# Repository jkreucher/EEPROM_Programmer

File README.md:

# Simple EEPROM Programmer

Copyright 2021 Jannik Kreucher

## Table of Contents
 - [Project](#project)
 - [Dependencies](#dependencies)
 - [Make](#make)
 - [Flash EEPROM](#flash-eeprom)
 - [Schematic](#schematic)
   - [Processor](#micro-processor)
   - [Shift Registers](#shift-registers)
   - [EEPROM](#eeprom)
 - [PCB](#pcb)
 - [Enclosure](#enclosure)
 - [License](#license)

## Project

I created this programmer for my personal Z80 project. Since commerical programmers are fairly expensive I created my own simple programmer. It is nothing fancy and just supports a single family of [EEPROMs](https://en.wikipedia.org/wiki/EEPROM). It does not have support for a higher programming voltage and is limited for +5V EEPROMs.

This simple programmer supports following EEPROMs:
 - [28c64 (8k)](http://ww1.microchip.com/downloads/en/devicedoc/doc0001h.pdf)
 - [28c256 (32k)](http://ww1.microchip.com/downloads/en/DeviceDoc/doc0006.pdf)

## Dependencies

To compile the code you need to have following tools installed:
 - avr-gcc (with avr-libs)
 - avrdude
 - uisp

The programmer flash tool uses [Python3](https://www.python.org/) and [pySerial](https://pyserial.readthedocs.io/en/latest/pyserial.html):
 - python3
 - python3-serial

The Makefile contains a command to install everything needed:
```
cd code
sudo make tools
```

## Make

First compile the ATmega code. Execute following in the project root folder:
```
cd code
make
```

Now flash the compiled code to the programmer. *Connect the ISP-Programmer* and execute:
```
make fuses
make upload
```
I am using a USBasp Programmer. **Note: Notch on ISP-Programmer must be facing the ATmega8 chip (U1) while flashing firmware.**

## Flash EEPROM

**Note: Firmware needs to be flashed beforehand !**

To flash your binary file to the EEPROM inserted type:
```
cd code
chmod +x eeprom.py
./eeprom.py -e -o -p /dev/ttyACM0 -b 115200 -w <binaryfile.bin>
```

For more information:
```
./eeprom.py -h
```

## Schematic

### Micro Processor
The micro processor used in this project is the popular [ATmega8 (U1)](https://ww1.microchip.com/downloads/en/DeviceDoc/Atmel-2486-8-bit-AVR-microcontroller-ATmega8_L_datasheet.pdf), a cheaper version of the ATmega328 used in the [Arduino Uno](https://store.arduino.cc/arduino-uno-rev3). It handles everything: the serial communication, address bus and the data bus. U2 (MCP2221) handles the USB to UART conversion so no external ftdi cable is needed. The supply voltage is conveniantly given by the USB port also. Because data bus of the EEPROM is bidirectional it is directly connected to the processor. The micro processor needs to handle setting the bus as input or output. See [`eeprom.c`](code/eeprom.c) for everything I/O related. The UART is handled in [`uart.c`](code/uart.c). And the communication protocol is defined in [`parser.c`](code/parser.c) and in [`main.c`](code/main.c).

### Shift Registers
The shift registers (U3, U4) are utilized to expand the IO of the processor. Just 3 bits are needed to set the address bus to the target address. Since the address bus is only one way no data needs to be read from the address bus thus making shift registers the obvious choice for this situation. See [`eeprom.c: addrbus_set()`](code/eeprom.c) for how the data is latched.

### EEPROM

The EEPROM uses a parallel interface for communication. The address bus (A0-A14) is a parallel input which sets the memory location to read or write. The control lines ~WE and ~OE (active low) tell the EEPROM to read or write from/to the memory. The data is read from or sent out the parallel data bus (D0-D7) depending on the state of the control lines. Some EEPROMs have Write-Protect enabled. A algorithm (see datasheet) is implemented to deactivate write protection. See [`eeprom.c: eeprom_disable_protect()`](code/eeprom.c) for how this works.

## PCB

Note: The pcb is designed so that the top layer represents jumpers. The vias are large enough to stick a wire through.

For the schematic and pcb layout I used [KiCad](https://kicad.org/), a very awsome open source EDA. The clearances and spaces are designed for diy home etching so nothing really fancy. See [`eeprom_programmer_bom.pdf`](bom/eeprom_programmer_bom.pdf) for the bill of materials. At the moment the whole project would cost you around 26€ plus a weekend of time.

## Enclosure

The very simple, easy and fast to print enclosure consists of two parts which sandwhich the pcb. Needed are just *4x M3,5x12mm* wood screws to assemble the enclosure.

## License

[MIT](LICENSE) Jannik Kreucher

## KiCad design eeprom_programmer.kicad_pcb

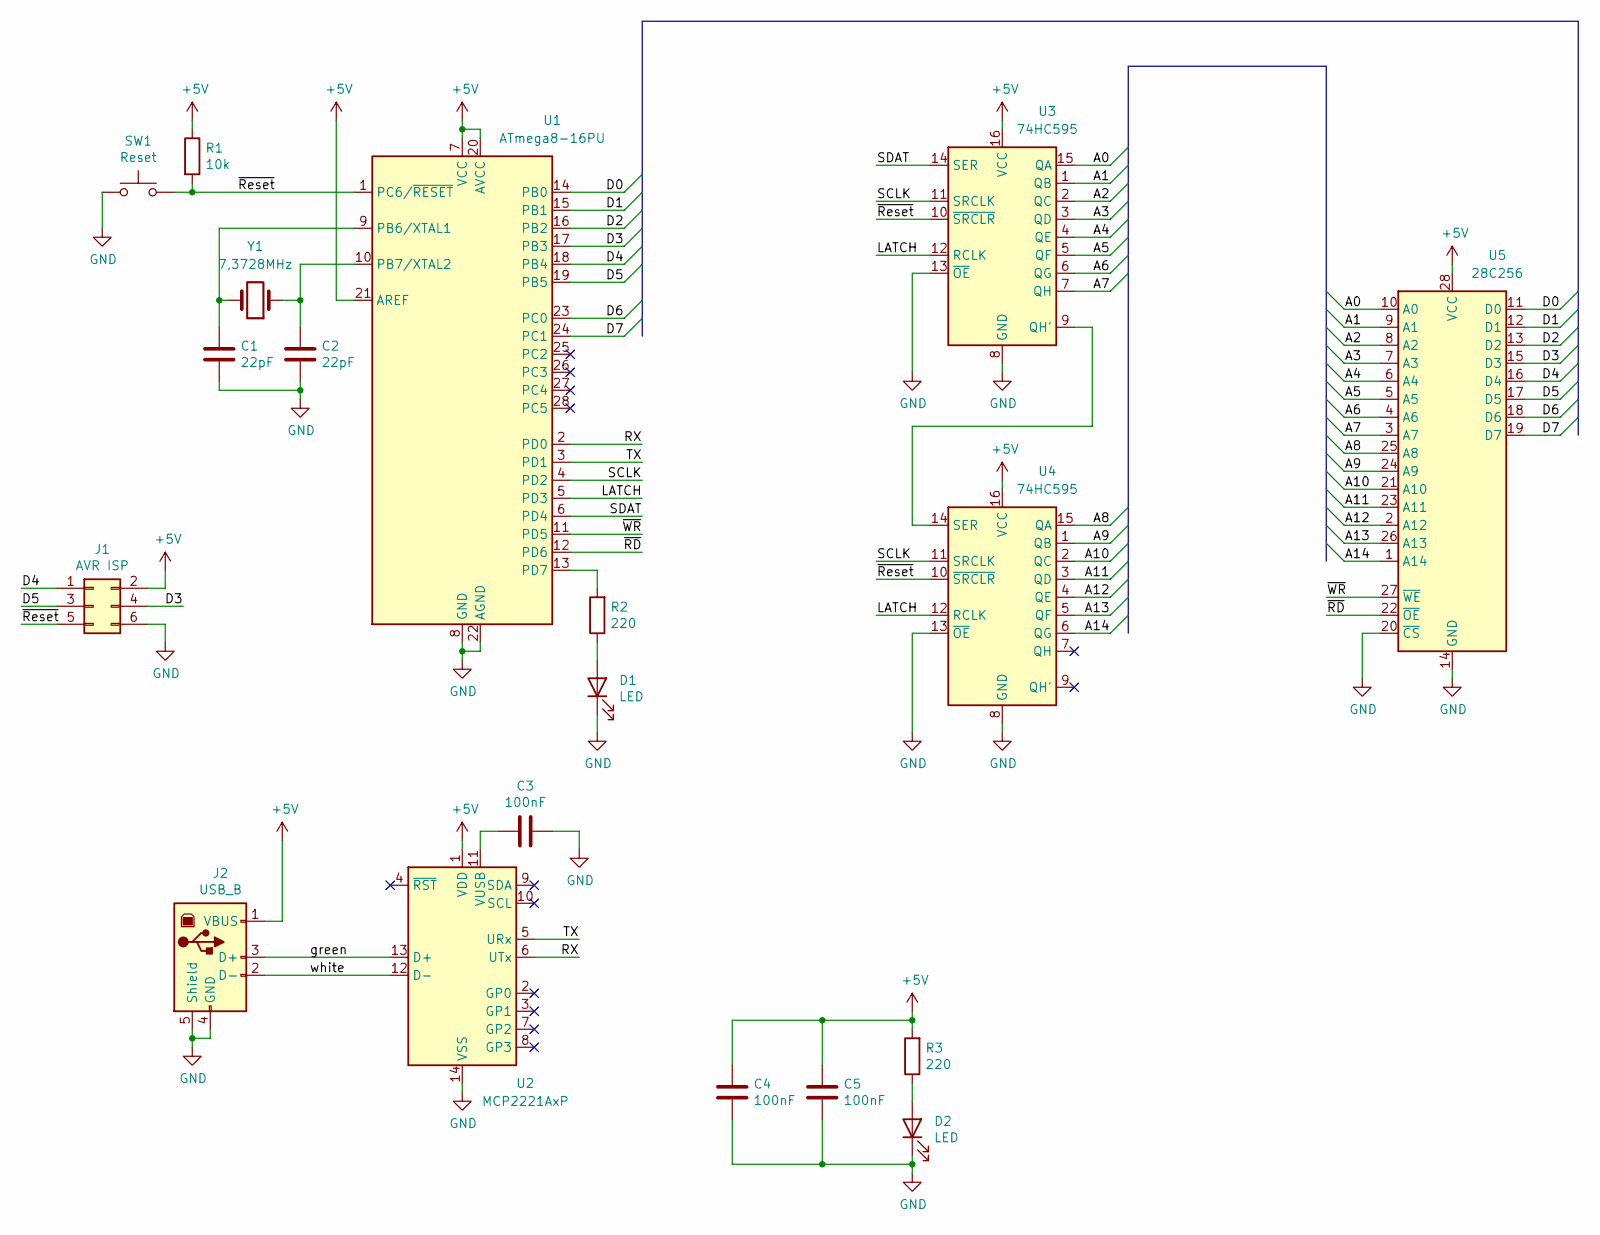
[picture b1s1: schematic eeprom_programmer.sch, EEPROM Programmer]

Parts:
C1, C2: 22pF; C_Disc_D3.0mm_W2.0mm_P2.50mm
C3, C4, C5: 100nF; C_Disc_D3.0mm_W2.0mm_P2.50mm
D1, D2: LED; LED_D5.0mm
J1: AVR ISP; PinHeader_2x03_P2.54mm_Vertical
J2: USB_B; USB_B_Lumberg_2411_02_Horizontal
R1: 10k; R_Axial_DIN0207_L6.3mm_D2.5mm_P10.16mm_Horizontal
R2, R3: 220; R_Axial_DIN0207_L6.3mm_D2.5mm_P10.16mm_Horizontal
SW1: Reset; SW_PUSH_6mm
U1: ATmega8-16PU; DIP-28_W7.62mm_LongPads
U2: MCP2221AxP; DIP-14_W7.62mm_LongPads
U3, U4: 74HC595; DIP-16_W7.62mm_LongPads
U5: 28C256; DIP-28_W15.24mm_ZIF_LongPads
Y1: 7,3728MHz; Crystal_HC49-U_Vertical

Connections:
+5V: C4.1, C5.1, J1.2, J2.1 (VBUS), R1.1, R3.2, U1.7 (VCC), U1.20 (AVCC), U1.21 (AREF), U2.1 (VDD), U3.16 (VCC), U4.16 (VCC), U5.28 (VCC)
/A0: U3.15 (QA), U5.10 (A0)
/A1: U3.1 (QB), U5.9 (A1)
/A2: U3.2 (QC), U5.8 (A2)
/A3: U3.3 (QD), U5.7 (A3)
/A4: U3.4 (QE), U5.6 (A4)
/A5: U3.5 (QF), U5.5 (A5)
/A6: U3.6 (QG), U5.4 (A6)
/A7: U3.7 (QH), U5.3 (A7)
/A8: U4.15 (QA), U5.25 (A8)
/A9: U4.1 (QB), U5.24 (A9)
/A10: U4.2 (QC), U5.21 (A10)
/A11: U4.3 (QD), U5.23 (A11)
/A12: U4.4 (QE), U5.2 (A12)
/A13: U4.5 (QF), U5.26 (A13)
/A14: U4.6 (QG), U5.1 (A14)
/D0: U1.14 (PB0), U5.11 (D0)
/D1: U1.15 (PB1), U5.12 (D1)
/D2: U1.16 (PB2), U5.13 (D2)
/D3: J1.4, U1.17 (PB3), U5.15 (D3)
/D4: J1.1, U1.18 (PB4), U5.16 (D4)
/D5: J1.3, U1.19 (PB5), U5.17 (D5)
/D6: U1.23 (PC0), U5.18 (D6)
/D7: U1.24 (PC1), U5.19 (D7)
/LATCH: U1.5 (PD3), U3.12 (RCLK), U4.12 (RCLK)
/RX: U1.2 (PD0), U2.6 (UTx)
/SCLK: U1.4 (PD2), U3.11 (SRCLK), U4.11 (SRCLK)
/SDAT: U1.6 (PD4), U3.14 (SER)
/TX: U1.3 (PD1), U2.5 (URx)
/green: J2.3 (D+), U2.13 (D+)
/white: J2.2 (D-), U2.12 (D-)
/~RD: U1.12 (PD6), U5.22 (~OE)
/~Reset: J1.5, R1.2, SW1.2, U1.1 (PC6/~RESET), U3.10 (~SRCLR), U4.10 (~SRCLR)
/~WR: U1.11 (PD5), U5.27 (~WE)
GND: C1.2, C2.2, C3.1, C4.2, C5.2, D1.1 (K), D2.1 (K), J1.6, J2.4 (GND), J2.5 (Shield), SW1.1, U1.8 (GND), U1.22 (AGND), U2.14 (VSS), U3.8 (GND), U3.13 (~OE), U4.8 (GND), U4.13 (~OE), U5.14 (GND), U5.20 (~CS)
unnamed: C1.1, U1.9 (PB6/XTAL1), Y1.2
unnamed: C2.1, U1.10 (PB7/XTAL2), Y1.1
unnamed: C3.2, U2.11 (VUSB)
unnamed: D1.2 (A), R2.1
unnamed: D2.2 (A), R3.1
unnamed: R2.2, U1.13 (PD7)
unnamed: U3.9 (QH'), U4.14 (SER)

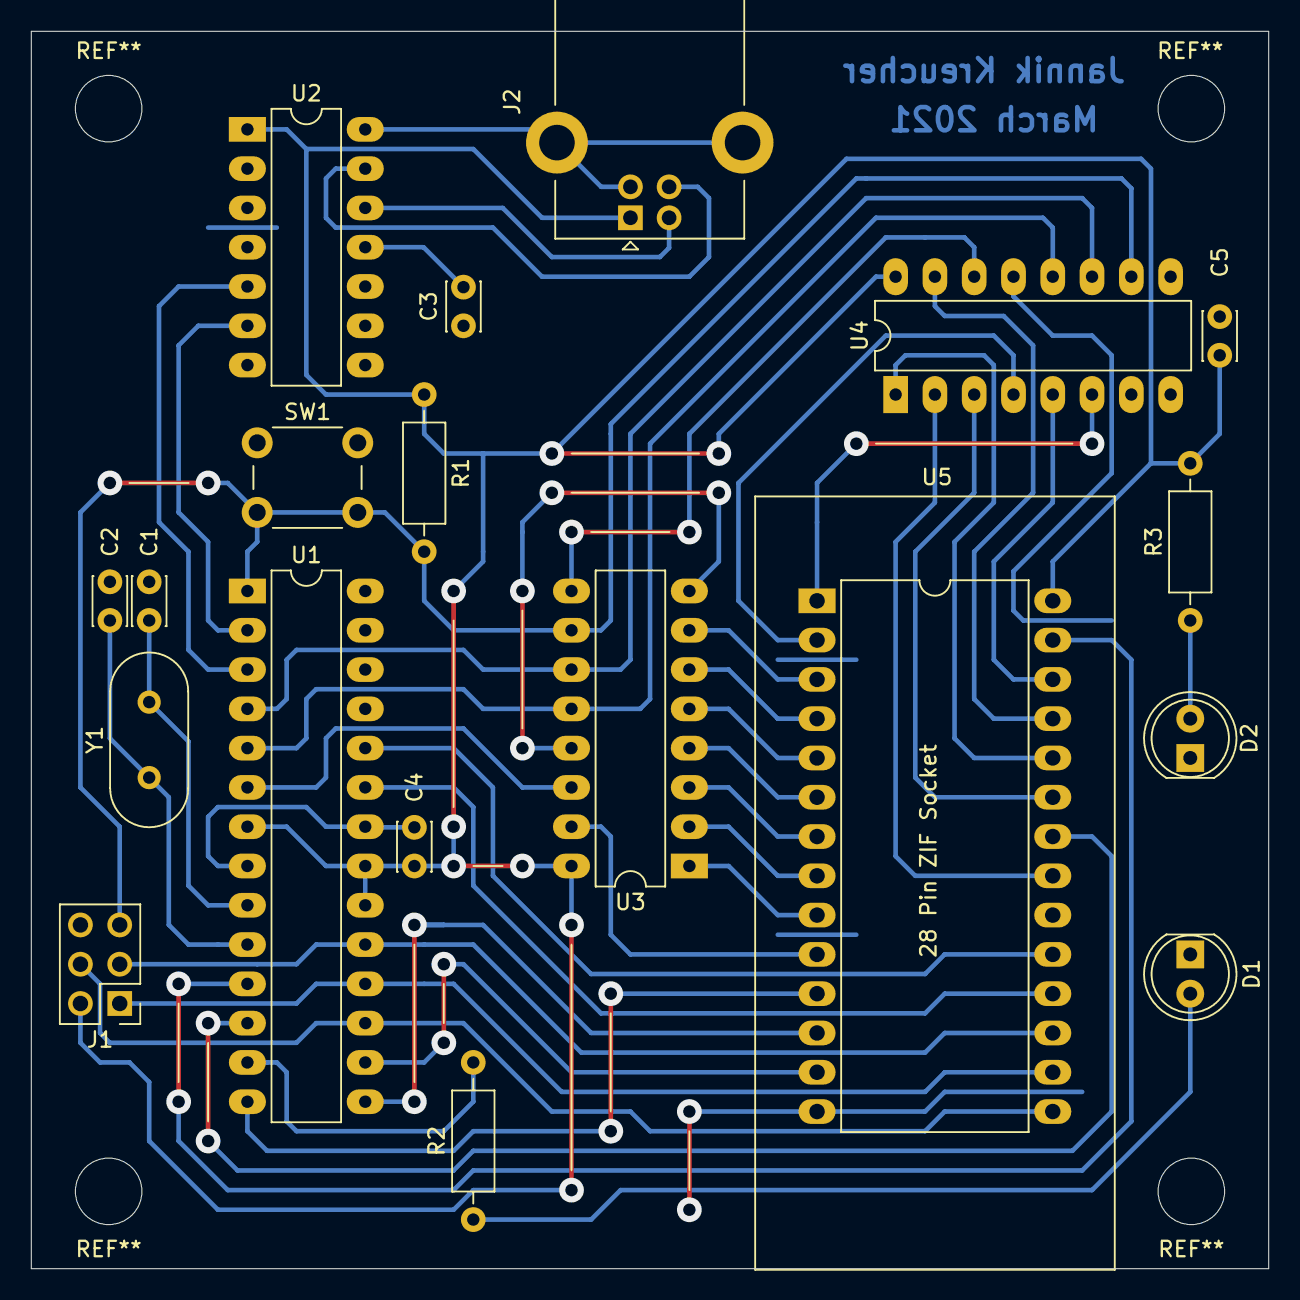
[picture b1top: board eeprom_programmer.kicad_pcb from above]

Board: 2 copper layers, 80.0 x 80.0 mm, 19 parts (0 on the bottom side), 42 nets.

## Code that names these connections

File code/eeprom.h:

#ifndef EEPROM_H_
#define EEPROM_H_

#include <avr/io.h>
#include <util/delay.h>

#define PIN_SCLK	(1<<2) // PD2: Shift Register Serial Clock
#define PIN_LATCH	(1<<3) // PD3: Shift Register RClock
#define PIN_SDAT	(1<<4) // PD4: Shift Register Serial Data
#define PIN_WR		(1<<5) // PD5: EEPROM Write Enable (active low)
#define PIN_RD		(1<<6) // PD6: EEPROM Read Enable (active low)
#define PIN_LED		(1<<7) // PD7: Status LED


void eeprom_init();

void databus_input();
void databus_output();

void databus_set(unsigned char data);
unsigned char databus_get();

void addrbus_set(unsigned short addr);

void eeprom_write(unsigned short addr, unsigned char data);
unsigned char eeprom_write_validate(unsigned short addr, unsigned char data);
unsigned char eeprom_read(unsigned short addr);

void eeprom_disable_protect();

#endif

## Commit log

2021-03-07 readme enclosure picture
2021-03-07 readme picture text
2021-03-07 readme add
2021-03-07 readme schematic
2021-03-07 readme overlay picture
2021-03-07 remove overlay from readme
2021-03-15 eeprom.py serial flush fix
2021-03-15 eeprom.py flush delay
2021-03-15 delay adjust
2021-03-16 eeprom.py progress bar rounding fix
2021-03-18 parser reverse order fix
2021-07-13 Add Picture
